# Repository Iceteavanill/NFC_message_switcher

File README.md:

[comment]: <> "LTeX: language=en-GB"

# NFC message switcher

This project is an implementation of an NFC tag which is able to change the message. It communicates to a host device. It was developed to be quickly assembled and easy to use but still be a bit more than a blinking light. It uses the reference implementation for the [bare metal TWI driver](https://github.com/microchip-pic-avr-examples/attiny1627-bare-metal-twi-mplab).

## Main principle of operation

The main device is the [ST25DV04K](https://www.st.com/resource/en/datasheet/st25dv04k.pdf). 
It can communicate via NFC and I2C. 
When an NFC capable device is held near the PCB, the ST25DV04K starts to receive power and starts communicating with the device. 
The Power that's transmitted is shared (energy harvesting mode) with a [ATtiny402](http://ww1.microchip.com/downloads/en/DeviceDoc/ATtiny202-402-AVR-MCU-with-Core-Independent-Peripherals_and-picoPower-40001969A.pdf). 
When powered it starts communicating via I2C and writes to the user accessible memory. 
When the written data has been confirmed, it powers down.

## Details

### Power

Power provider is the energy harvesting mode of the ST25DV04K, the power source is a NFC capable device that is in proximity of the PCB.
It is buffered via a 47μF capacitor.
Because of that, it is essential to keep the power consumption of the ATtiny as low as possible.
Consult the source code for more details.

### Link arbitration

The ST25DV04K does only support I2C *or* NFC active at the same time. 
However, it has an open drain output that can be used to sense the current activity. 
Low, signals that the device is currently busy. 
The ATtiny then waits for the device to be available, by waiting in sleep. 
A hardware interrupt is not yet implemented.

### Device configuration

The ST25DV04K needs some configuration for correct operation. 
The energy harvesting mode must be enabled/forced at startup. 
Also, the GPO mode must be set to RF_ACTIVITY_EN to enable better link arbitration.
The configuration happens after the ATtiny has been programmed once.

### Antenna

The antenna / coil design is based on a [paper](https://www.researchgate.net/publication/339137261_Inductance_Formula_for_Rectangular_Planar_Spiral_Inductors_with_Rectangular_Conductor_Cross_Section) from Hubert Aebischer. 
The ST25DV04K has an internal tuning capacitor which should be assumed to be 29pF.
Based on that, the inductance should be 4.75μH. 

### Formfactor

The PCB dimensions are the same as a credit card.
It is however quite a bit thicker.

# Building your own

All required files to recreate this project can be found [here](https://github.com/Iceteavanill/NFC_message_switcher/releases/tag/1.0.0). 

## Sourcing

The following parts are needed to recreate this Project (as well as the PCB):

| Reference 	|   Value   	| Qty 	|    Digikey number    	|
|:---------:	|:---------:	|:---:	|:-------------------:	|
|   C1, C3   	|   0.1uF   	|  2  	|    1276-1000-1-ND   	|
|     C2    	|    47uF   	|  1  	|    1276-3063-2-ND   	|
|   R1, R2   	|    4k7    	|  2  	|    MMA-4.7KACT-ND   	|
|     U1    	| ATtiny402 	|  1  	| ATTINY402-SSNRCT-ND 	|
|     U2    	| ST25DV04K 	|  1  	|    497-17123-1-ND   	|

## Assembly

There are no special requirements for the assembly of the PCB's. 
If you are used to soldering SMD components it shouldn0t be a problem. 

## Software

You can use the provided released hex file, however it is recommended to customize the software to your own taste. 

There are multiple options to customize the software

> [!WARNING]  
> I tried making the process of using the software as easy as possible, however it may not be very easy/beginner-friendly in places.

### Overview

Customizing the software always requires a rebuild of the firmware of the Attiny. 
The XC8 compiler from microchip is recommended. 
The following flags were used and are recommended:

| Flags    | commands                                                                   |
|----------|----------------------------------------------------------------------------|
| Global   | -gdwarf-3 -mconst-data-in-progmem -mno-const-data-in-config-mapped-progmem |
| compiler | -funsigned-char -funsigned-bitfields -Wall -O2 -fno-common                 |
| linker   | "libm" -Wl,--gc-sections                                                   |

A makefile is already prepared with all the required flags. 
If you install a later version you might have to alter the paths a little.

For customization, only a header file has to be altered (```nfc_messages.h```).  
There are multiple ways of accomplishing that:

 * editing the header directly (not recommended)
 * using the python script
 * using the gui (recommended)

### Editing the header directly

Editing the header directly is not recommended because the required data must be in the NDEF format. 
Manually generating that is very tedious. 
If you have special needs however, like encoding special data types, you have to do it this way because anything else has not been implemented.

### Using the pyton script

The ```dataGenerator.py``` python script can be used to quickly generate custom messages. 
It requires the NDEFLib python library. 
Edit the ```message_as_text_list``` list with your messages and then run the script:
```py
message_as_text_list = ["Test 1",
                        "Test 2 a bit longer",
                        "Test 3 even looooooooooooooooooooooooooonger",
                        "https://www.youtube.com/watch?v=dQw4w9WgXcQ",
                        "spotify:track:4cOdK2wGLETKBW3PvgPWqT"
]
```
### Using the gui

A gui has been made to quickly program multiple NFC tags. 
It requires WXpython and uses the previously mentioned script and the ```message_as_text_list```.
For uploading, it relies on the MPLAB IPE programming software and its command line interface.

Programming steps:

1. Step:

Enter your desired message(s) in the table at the top. 
Links to websites videos or Spotify songs are also allowed.

2. Step:

If your main device is an iPhone check the ```iPhone compatability mode```. 
IPhones are unable to read text from a NFC device, and the text messages have to be encoded as a website.

3. Step:

Some default messages are added to the list automatically. If you don't want that, you can disable that with the checkbox ```Remove predefined texts```. 
The ```message_as_text_list``` from ```dataGenerator.py``` is used as a source.

4. Step:

Connect your programmer to the tag and press program device. 
The build and upload steps are automatically executed.

### Building and uploading

In all options but the gui you have to manually build and then upload the firmware. 
You can use the ``` make upload ``` command with the option ``` PROGTOOL= ``` to select the programmer that you have on hand. 
See the documentation of the IPE programmer option to know which flag you have to use.

## Batch programming

Many devices in a row can be programmed with the programming jig:

It was designed in Onshape. 
I used pogopins that I had on hand. 
You probably want to customize it to your current stock. 
You find the Onshape document [here](https://cad.onshape.com/documents/450623688917edcaa975b9e7/w/39588c936aa9381f65fac7c0/e/be57d568f84f27791dc539d2?renderMode=0&uiState=67cfd948ca833f6780730f6a).

## Rating GUI

Because this PCB was designed as a competition PCB, a rating gui has been made using streamlit. 
You can import a CSV of contestants and rate each one for time, quality and some other points. 
It is meant to be customized to your particular use case. 

# Caveat

It must be noted that the current design has a (obvious) flaw. 
The ATtiny is in the middle of the coil and *probably* quite affected by the activity of it. 
When combined with the nonideal power delivery method, this can significantly impair functionality at times (The I2C content that is written gets verified but I2C has no error correcting method).
Some more analysis in that regard is not yet made.

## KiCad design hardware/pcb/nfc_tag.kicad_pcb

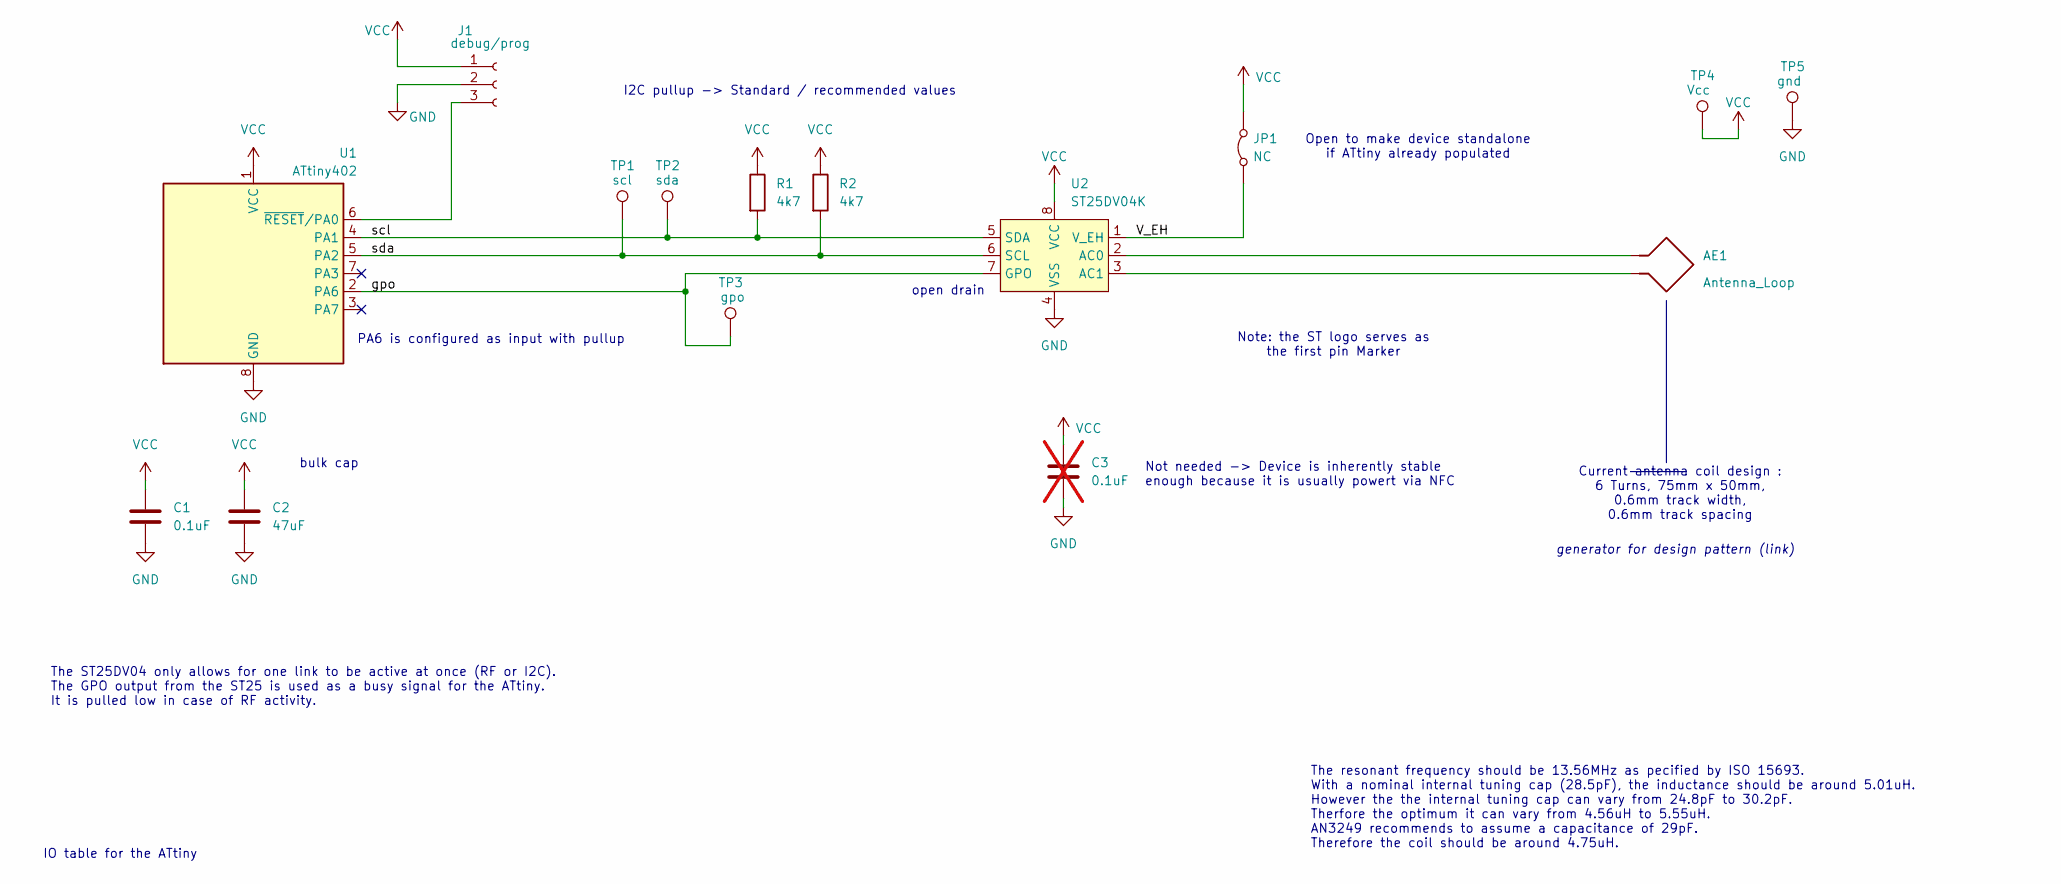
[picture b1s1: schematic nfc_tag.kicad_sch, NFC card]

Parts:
AE1: Antenna_Loop; nfc antenna_optimized
C1: 0.1uF; C_0603_1608Metric_Pad1.08x0.95mm_HandSolder; Digikeynumber 1276-1000-1-ND
C2: 47uF; C_1206_3216Metric_Pad1.33x1.80mm_HandSolder; Digikeynumber 1276-3063-2-ND
C3: 0.1uF; C_0603_1608Metric_Pad1.08x0.95mm_HandSolder; Digikeynumber 1276-1000-1-ND; not fitted
J1: debug/prog; debug_pads
JP1: NC; SolderJumper-2_P1.3mm_Bridged2Bar_RoundedPad1.0x1.5mm
R1, R2: 4k7; R_MiniMELF_MMA-0204; Digikeynumber MMA-4.7KACT-ND
TP1: scl; TestPoint_Pad_D1.5mm
TP2: sda; TestPoint_Pad_D1.5mm
TP3: gpo; TestPoint_Pad_D1.5mm
TP4: Vcc; TestPoint_Pad_D1.5mm
TP5: gnd; TestPoint_Pad_D1.5mm
U1: ATtiny402; SOIC-8_3.9x4.9mm_P1.27mm; Digikeynumber ATTINY402-SSNRCT-ND
U2: ST25DV04K; SOIC-8-1EP_3.9x4.9mm_P1.27mm_EP2.29x3mm; Digikeynumber 497-17123-1-ND

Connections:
/V_EH: JP1.1 (A), U2.1 (V_EH)
/gpo: TP3.1, U1.2 (PA6), U2.7 (GPO)
/scl: R1.2, TP2.1, U1.4 (PA1), U2.5 (SDA)
/sda: R2.2, TP1.1, U1.5 (PA2), U2.6 (SCL)
GND: C1.2, C2.2, C3.2, J1.2, TP5.1, U1.8 (GND), U2.4 (VSS)
unnamed: J1.3, U1.6 (~RESET/PA0)
unnamed: AE1.1, U2.2 (AC0)
unnamed: AE1.2, U2.3 (AC1)
VCC: C1.1, C2.1, C3.1, J1.1, JP1.2 (B), R1.1, R2.1, TP4.1, U1.1 (VCC), U2.8 (VCC)

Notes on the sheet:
The resonant frequency should be 13.56MHz as pecified by ISO 15693. With a nominal internal tuning cap (28.5pF), the inductance should be around 5.01uH. However the the internal tuning cap can vary from 24.8pF to 30.2pF. Therfore the optimum it can vary from 4.56uH to 5.55uH. AN3249 recommends to a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
Not needed -> Device is inherently stable enough because it is usually powert via NFC
IO table for the ATtiny
I2C pullup -> Standard / recommended values
The ST25DV04 only allows for one link to be active at once (RF or I2C). The GPO output from the ST25 is used as a busy signal for the ATtiny. It is pulled low in case of RF activity.
PA6 is configured as input with pullup
bulk cap
Current antenna coil design : 6 Turns, 75mm x 50mm, 0.6mm track width, 0.6mm track spacing
generator for design pattern (link)
open drain
Note: the ST logo serves as the first pin Marker
Open to make device standalone if ATtiny already populated

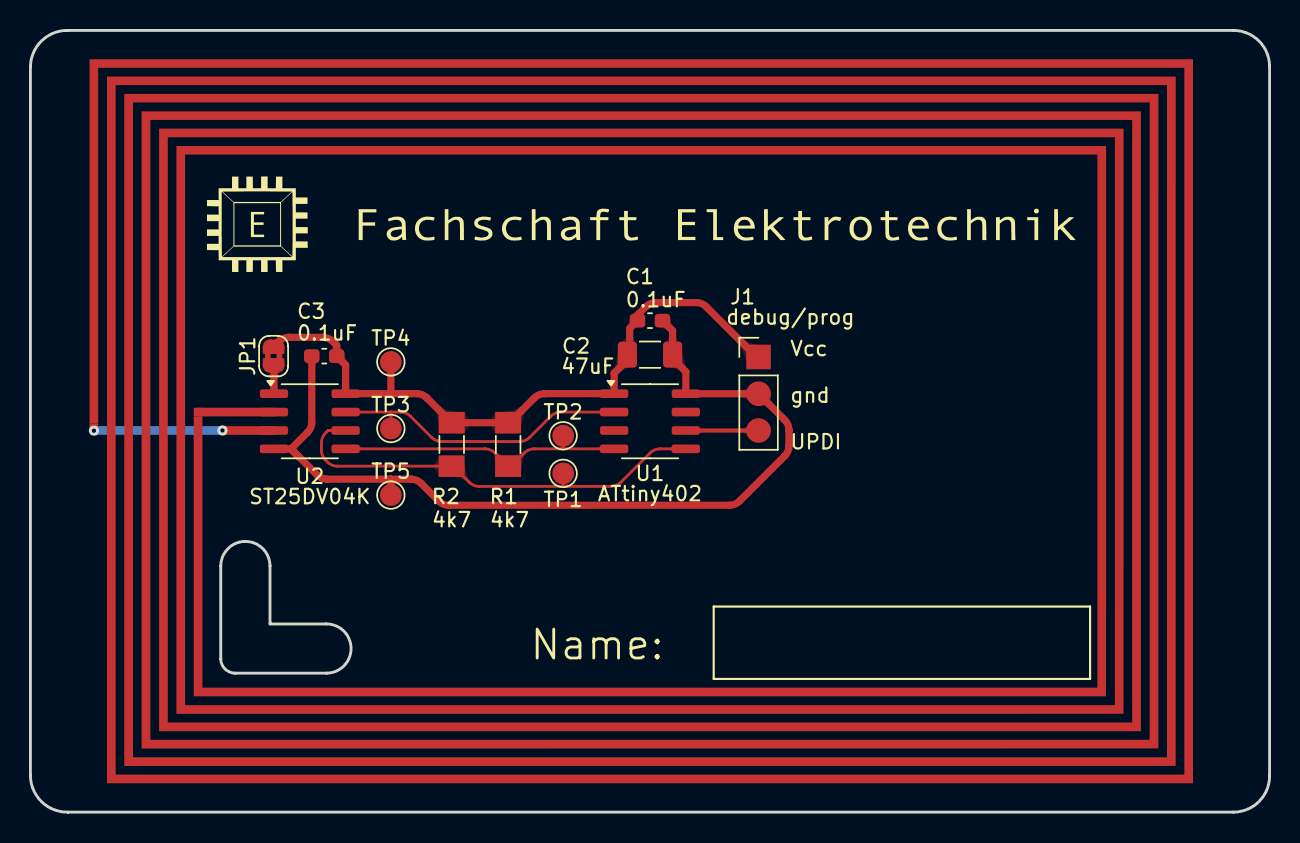
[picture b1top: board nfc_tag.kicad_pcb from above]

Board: 2 copper layers, 85.6 x 54.0 mm, 15 parts (0 on the bottom side), 9 nets.

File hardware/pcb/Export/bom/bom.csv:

"Reference","Value","Datasheet","Footprint","Qty","DNP","Digikeynumber"
"C1","0.1uF","~","Capacitor_SMD:C_0603_1608Metric_Pad1.08x0.95mm_HandSolder","1","","1276-1000-1-ND"
"C2","47uF","~","Capacitor_SMD:C_1206_3216Metric_Pad1.33x1.80mm_HandSolder","1",""," 1276-3063-2-ND"
"C3","0.1uF","~","Capacitor_SMD:C_0603_1608Metric_Pad1.08x0.95mm_HandSolder","1","DNP","1276-1000-1-ND"
"R1,R2","4k7","~","Resistor_SMD:R_MiniMELF_MMA-0204","2",""," MMA-4.7KACT-ND"
"U1","ATtiny402","http://ww1.microchip.com/downloads/en/DeviceDoc/ATtiny202-40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","Package_SO:SOIC-8_3.9x4.9mm_P1.27mm","1","","ATTINY402-SSNRCT-ND"
"U2","ST25DV04K","https://www.st.com/resource/en/datasheet/st25dv04k.pdf","Package_SO:SOIC-8-1EP_3.9x4.9mm_P1.27mm_EP2.29x3mm","1","","497-17123-1-ND"

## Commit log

2025-03-03 initial software commit debugging file for Analog discovery included
2025-03-04 initial hardware commit
2025-03-05 minor changes and corrections
2025-03-07 formatting changes added some functions
2025-03-08 Changed library to reference bare metal TWI drivers rewrote software accordingly edited jupyter notebook
2025-03-09 Added ReadMe and picture
2025-03-10 Changed picture
2025-03-11 added programming jig
2025-03-16 changed message length to extraction from message Enabled BOD (works very good) Added compilerflags to docs
2025-03-19 added dataGenerator.py. This script generates nfc_messages.h, which contains the encoded messages edites main.c accordingly Changed TWI_host TWI_sendBytesToRegister function to recieve const uint8_t.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
2025-03-26 added nfc_programmer_gui.py. This is a python programm that allows for quick custom programming of multiple nfc tags. It is implemented with the wxwidgets library and wxglade to generate the UI
    Edited dataGenerator.py to be usable by nfc_programmer_gui
    Added a makefile for the microcontroller code
    edited gitignore accordingly
2025-03-26 Made finaly hardware Export Edited color of PCB in file
2025-03-30 Added rating_gui. A streamlit application to speed up the rating of many PCB's. Added gitignore to accomodate a subfolder that gets written for a backup
2025-03-30 bugfixes mainly adding keys to critical buttons clearing search bar because it was making things difficult
2025-03-30 added error handling for the ipe programmer If programmer failed, it leaves lock and ini files behind. They now get automatically deleted.
2025-03-31 Changed layout for the programmer_gui Added web view for a html manual page added controls disable and wait warning
2025-03-31 Regenerated WX glade code.
2025-03-31 Added icon to menu bar
2025-03-31 Added progress bar to programming window
2025-04-01 changed clean command to include lock files because the IPE generates a lot Added a clean command in the gui added a textfield to edit the source path to the lock files
2025-04-01 Added needed_cols_dataset. if these cols are not present, it raises a error because they are needed Changed bool rating style from checkox to pills refactored and improved backup csv handling
2025-04-02 Added space compatability to the provided path added message to wating message
2025-04-03 improved schematic clarity and fixed sight mistake in csv
2025-04-05 Added some dociumentation Minor gui error handling enhancement and whitespace cleanup
2025-04-06 Enhanced documentation
2025-04-06 added proper manual to programmer gui
2025-04-10 Small improvement to manual added logging to programmer gui Added randomness to list setup
2025-04-13 Added delete Backupfile button Added another rating option
2025-04-13 removed whitespace
2025-04-16 Added fullscreen as default setting
